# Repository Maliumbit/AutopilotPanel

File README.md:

# AutopilotPanel
Autopilot Controller

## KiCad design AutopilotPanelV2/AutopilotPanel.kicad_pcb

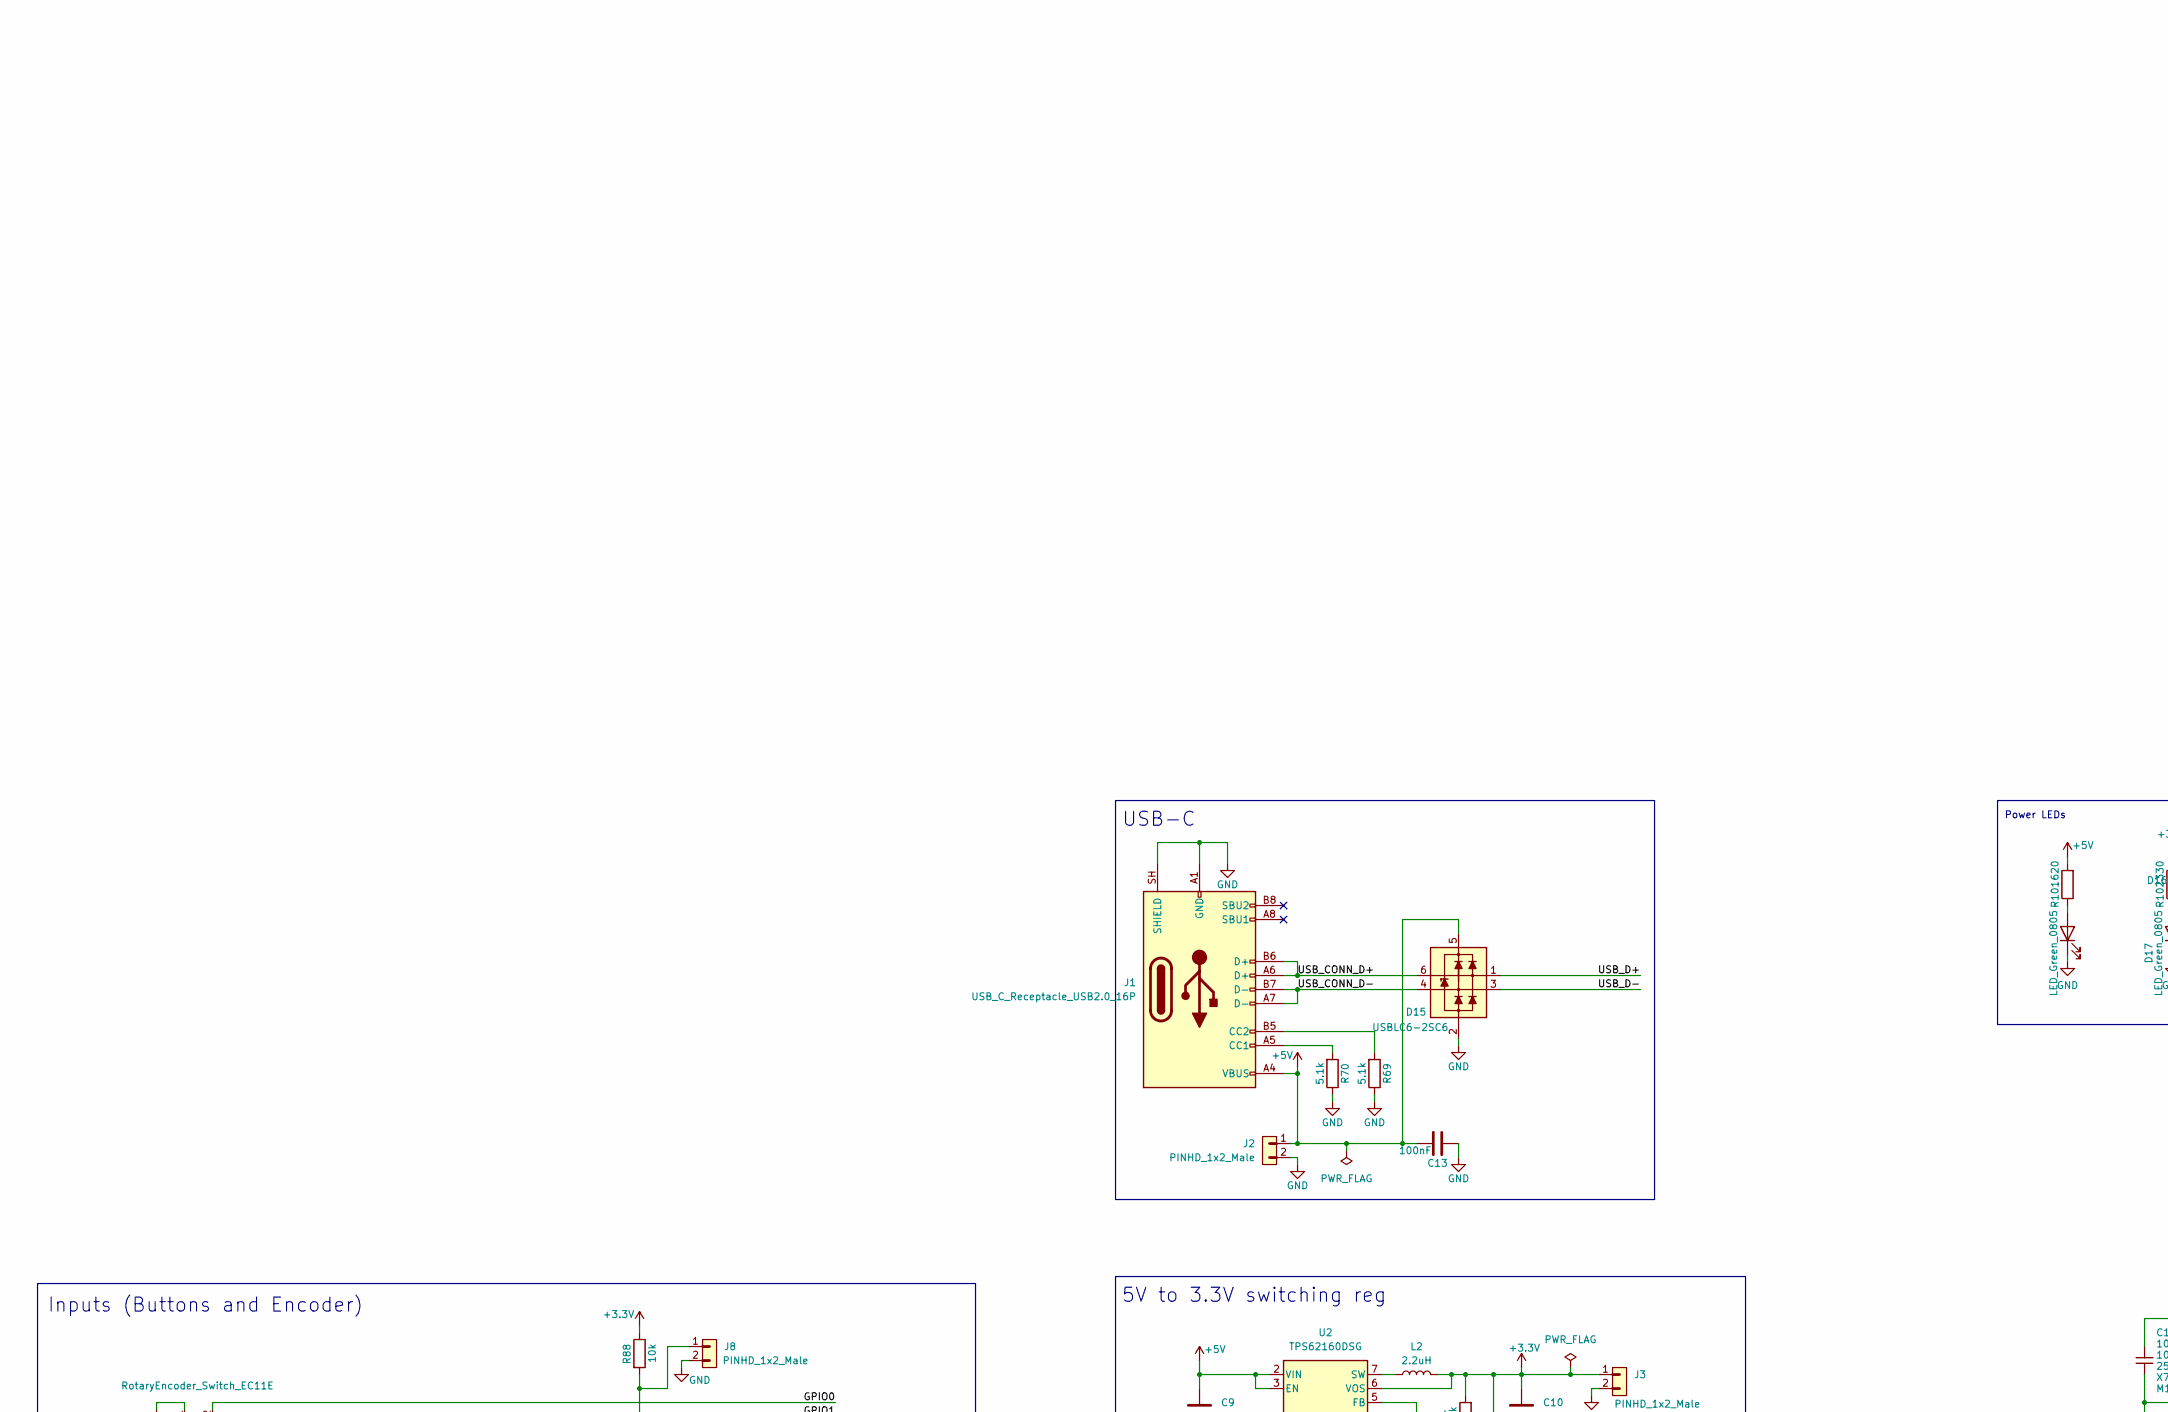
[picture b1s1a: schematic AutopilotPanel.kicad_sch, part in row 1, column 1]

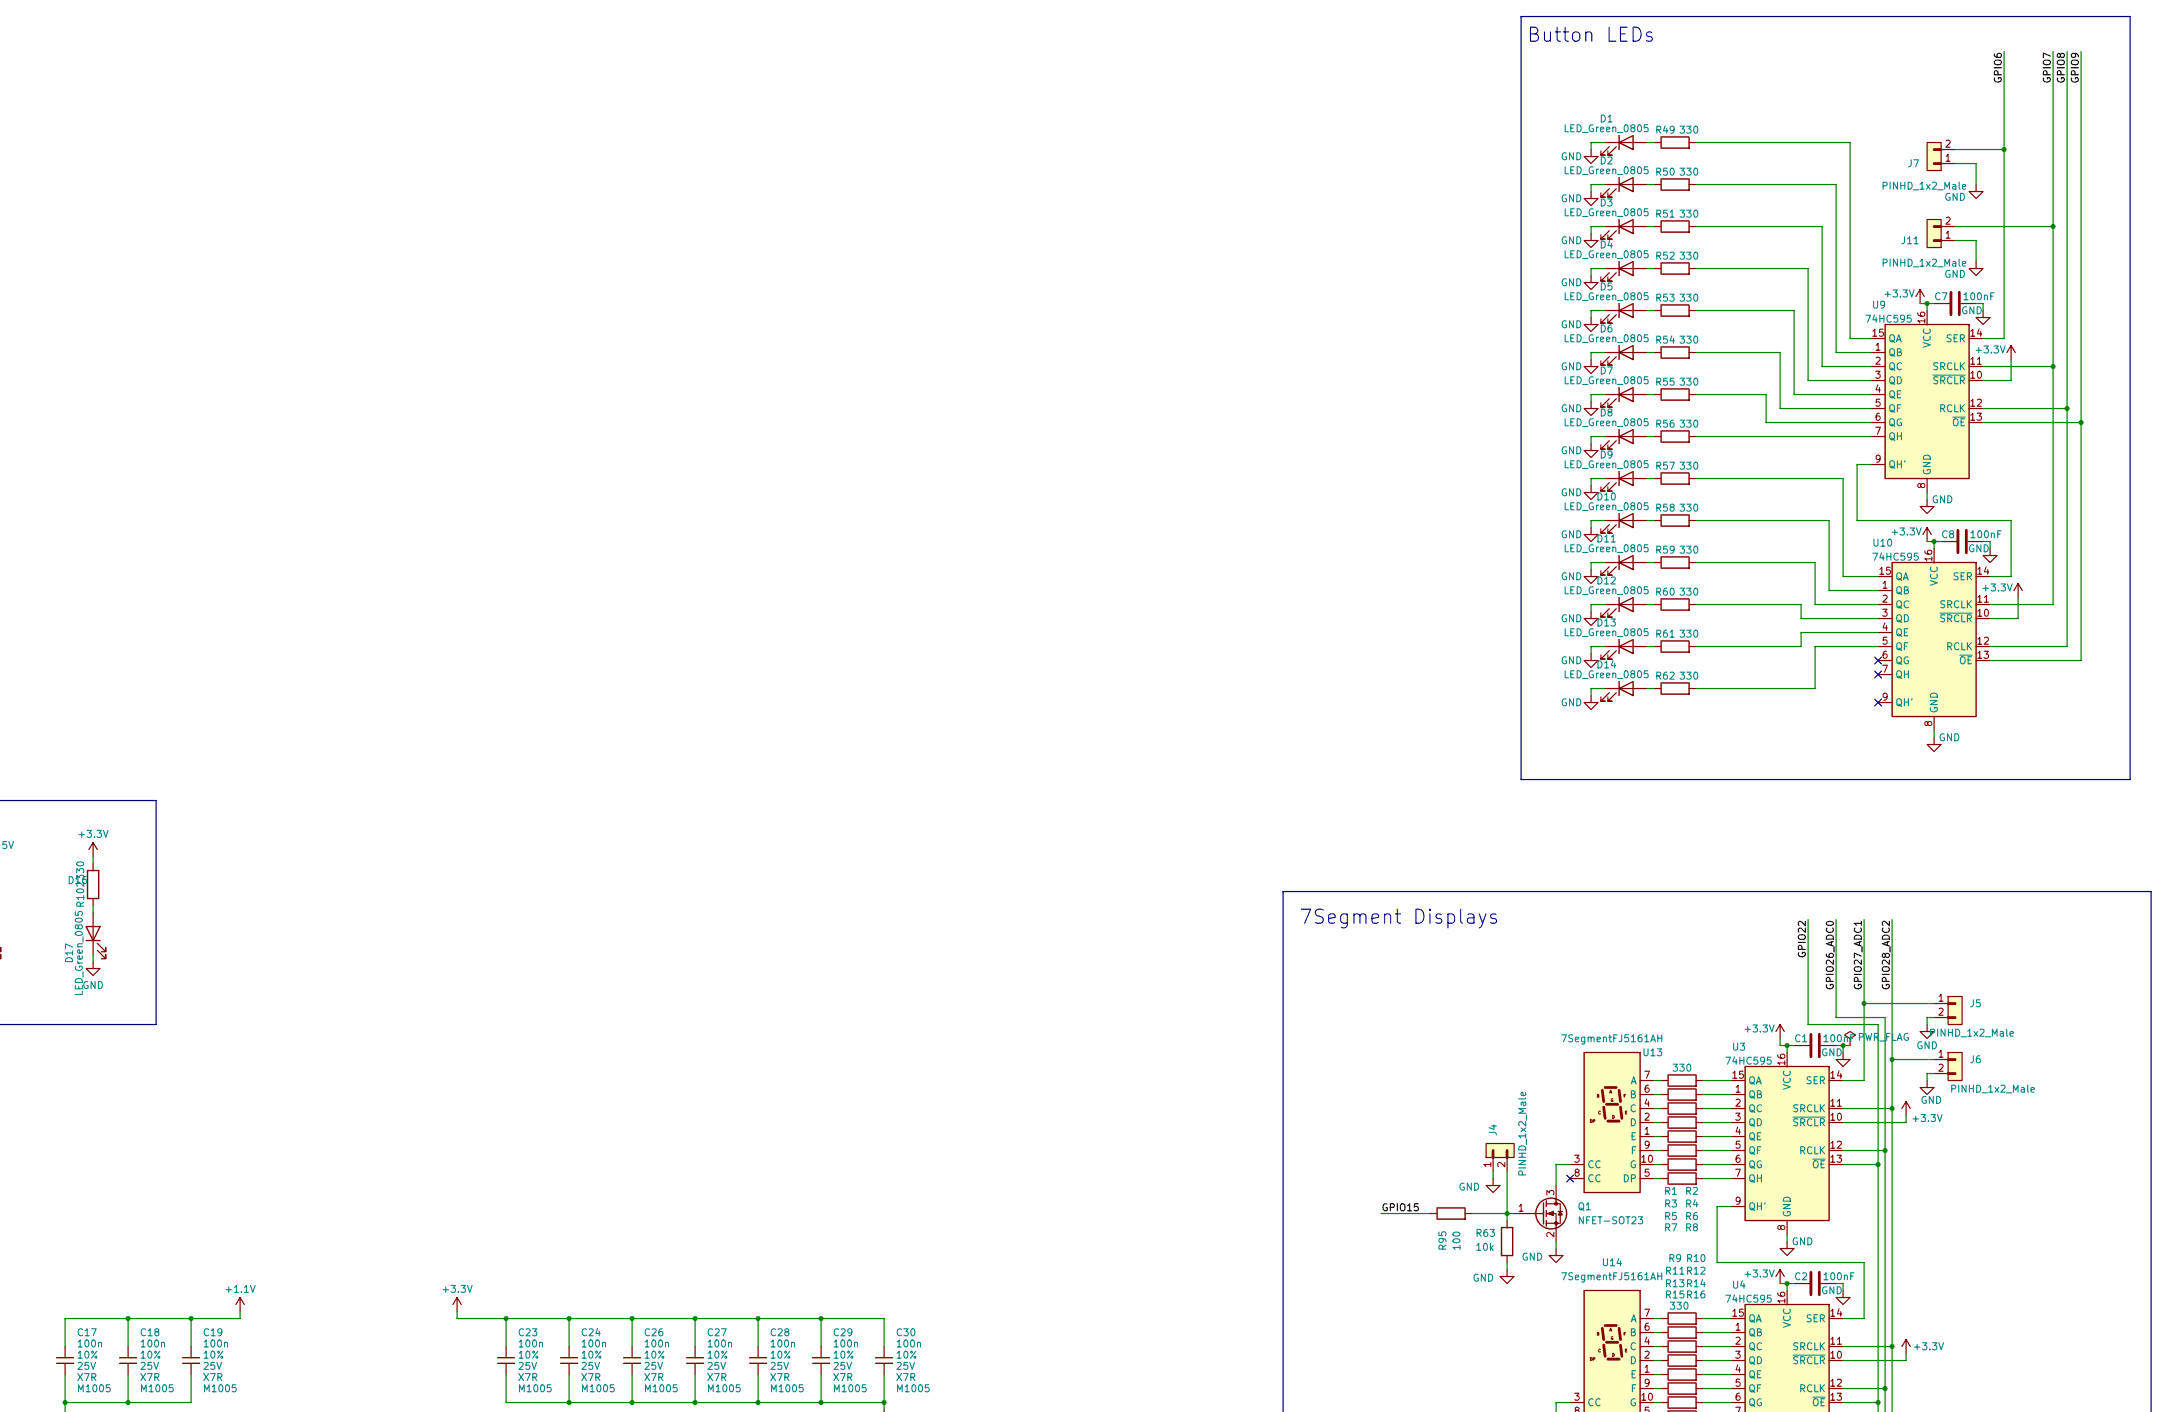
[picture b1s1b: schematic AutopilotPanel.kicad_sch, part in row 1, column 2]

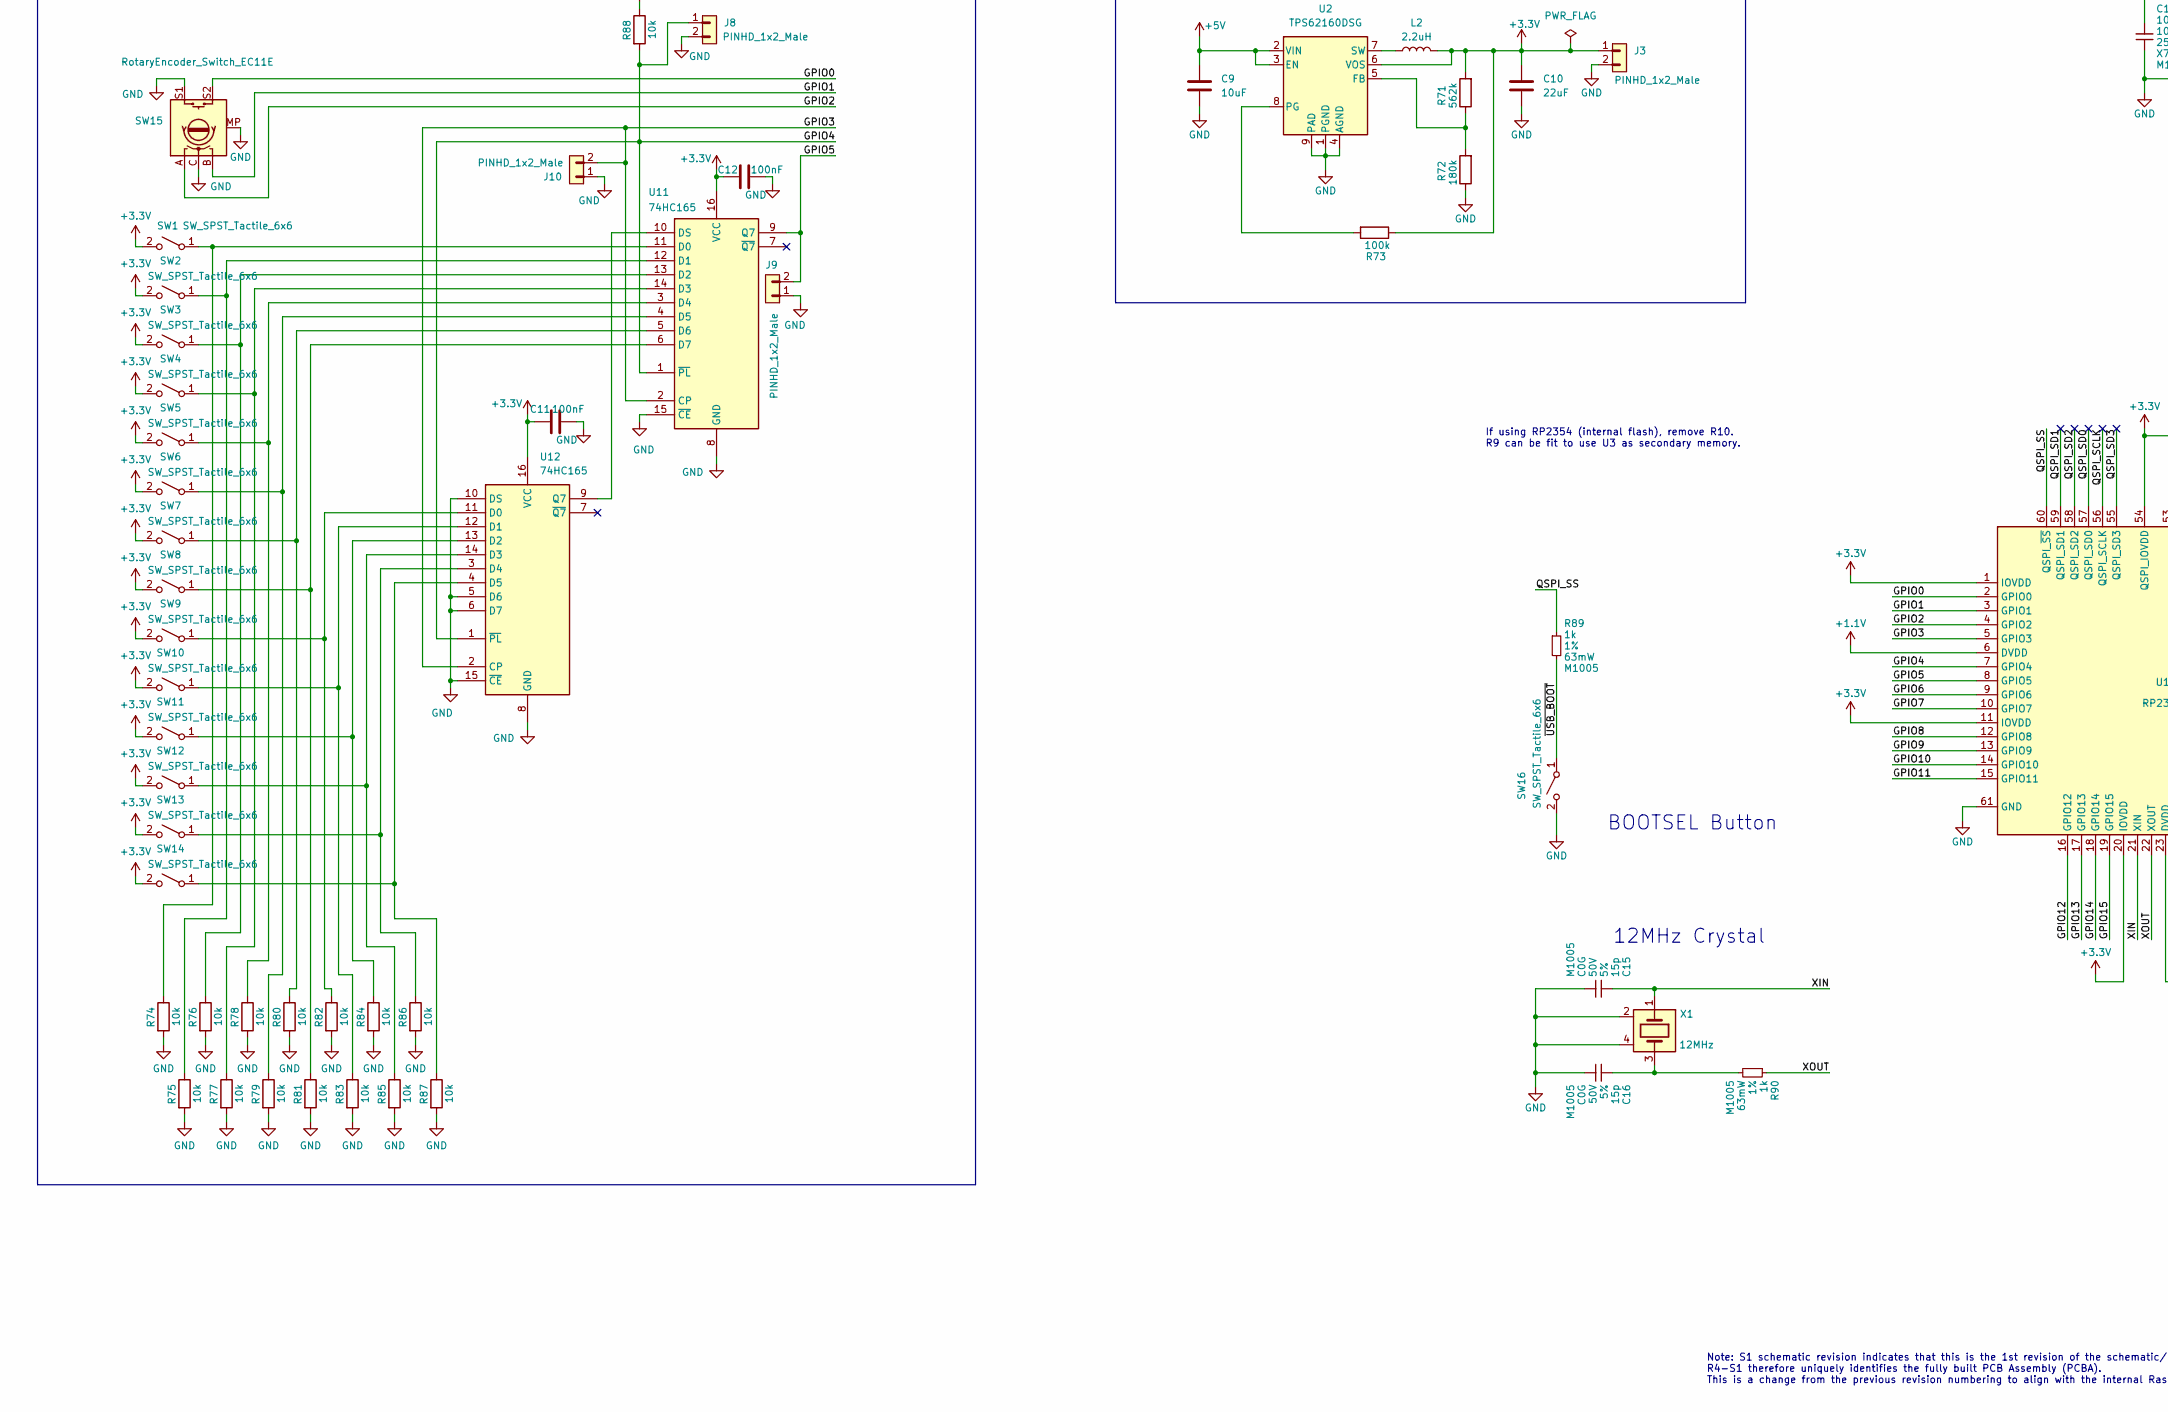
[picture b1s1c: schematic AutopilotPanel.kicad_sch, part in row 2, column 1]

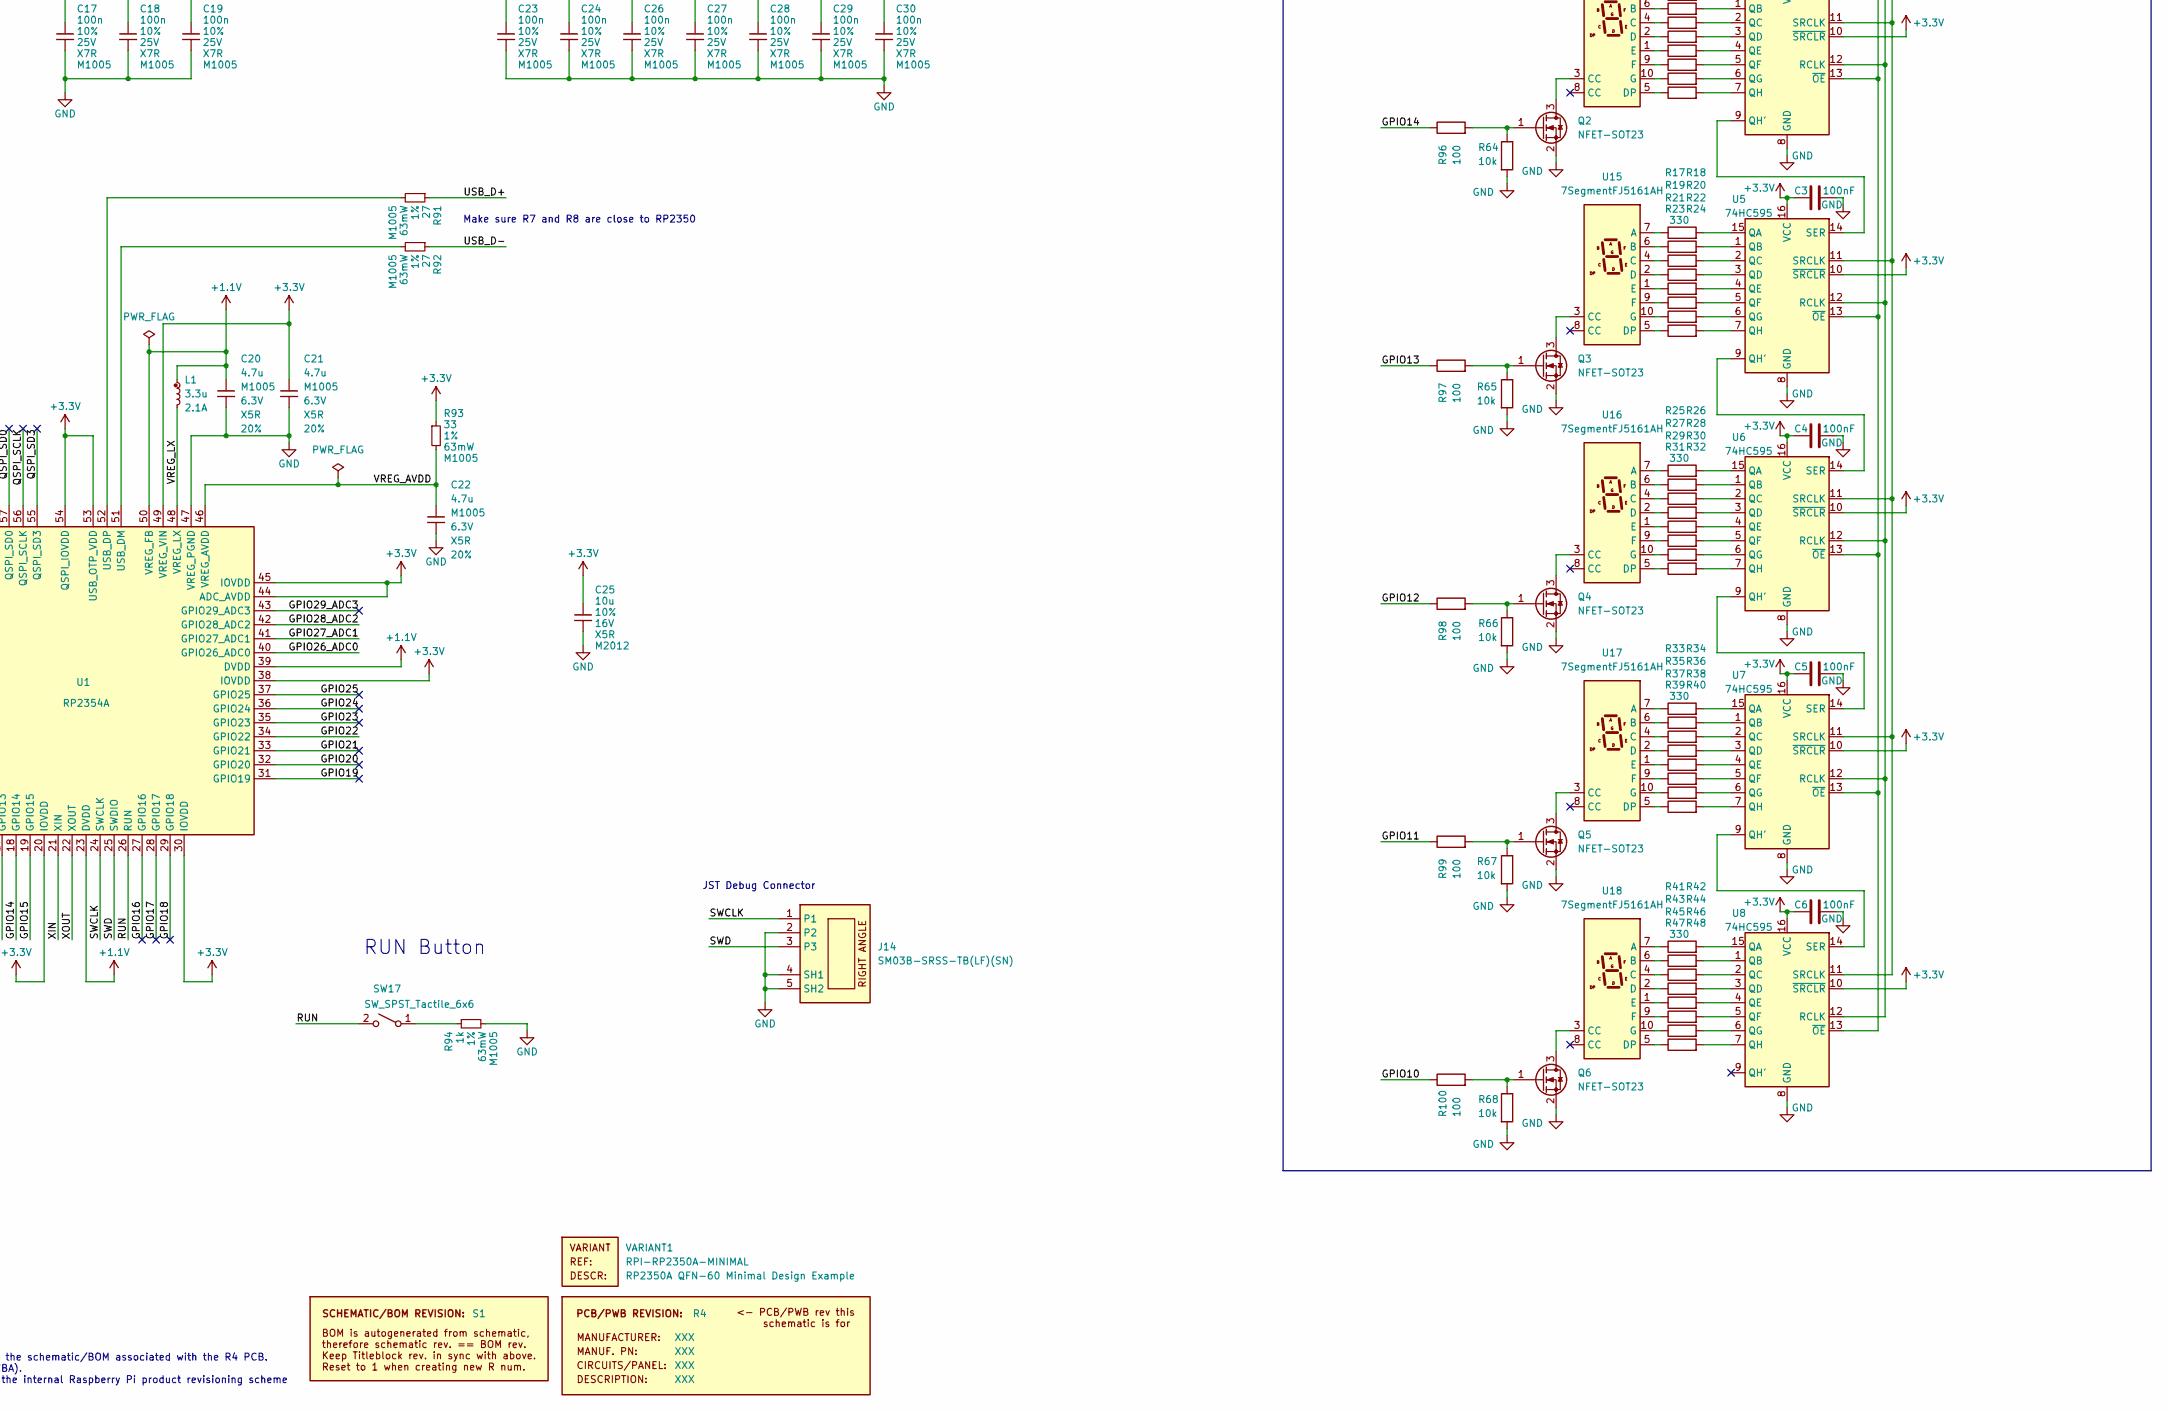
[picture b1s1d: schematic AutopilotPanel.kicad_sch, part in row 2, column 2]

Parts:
C1, C2, C3, C4, C5, C6, C7, C8, C11, C12, C13: 100nF; C_0603_1608Metric
C9: 10uF; C_0805_2012Metric
C10: 22uF; C_0805_2012Metric
C15, C16: 15p; C_0402_1005Metric; voltage 50V; tolerance 5%; part_uid RP-01C89W-LLY9XV
C17, C18, C19, C23, C24, C26, C27, C28, C29, C30: 100n; C_0402_1005Metric; voltage 25V; tolerance 10%; part_uid RP-01BJ9Y-KRGF41
C20, C21, C22: 4.7u; C_0402_1005Metric; voltage 6.3V; tolerance 20%; part_uid RP-019A1P-0C2GHY
C25: 10u; C_0805_2012Metric; voltage 16V; tolerance 10%; part_uid RP-01GYSK-AVBE41
D1, D2, D3, D4, D5, D6, D7, D8, D9, D10, D11, D12, D13, D14, D16, D17: LED_Green_0805; LED_0805_2012Metric_Pad1.15x1.40mm_HandSolder
D15: USBLC6-2SC6; SOT-23-6
J1: USB_C_Receptacle_USB2.0_16P; USB_C_Receptacle_G-Switch_GT-USB-7010ASV
J2, J3, J4, J5, J6, J7, J8, J9, J10, J11: PINHD_1x2_Male; PinHeader_1x02_P2.54mm_Vertical
J14: SM03B-SRSS-TB(LF)(SN); jst_sm03b-srss-tb-lf--sn-; part_uid RP-01EKJ1-8V9SV1
L1: 3.3u; abracon_aota-b201610s3r3-101-t; tolerance 20%; part_uid RP-01GY5D-2VC7WP
L2: 2.2uH; L_Changjiang_FNR3015S
PCB1: R4; manufacturer_pn XXX
Q1, Q2, Q3, Q4, Q5, Q6: NFET-SOT23; SOT-23
R1, R2, R3, R4, R5, R6, R7, R8, R9, R10, R11, R12, R13, R14, R15, R16, R17, R18, R19, R20, R21, R22, R23, R24, R25, R26, R27, R28, R29, R30, R31, R32, R33, R34, R35, R36, R37, R38, R39, R40, R41, R42, R43, R44, R45, R46, R47, R48, R49, R50, R51, R52, R53, R54, R55, R56, R57, R58, R59, R60, R61, R62, R102: 330; R_0603_1608Metric
R63, R64, R65, R66, R67, R68, R74, R75, R76, R77, R78, R79, R80, R81, R82, R83, R84, R85, R86, R87, R88: 10k; R_0603_1608Metric
R69, R70: 5.1k; R_0603_1608Metric
R71: 562k; R_0603_1608Metric
R72: 180k; R_0603_1608Metric
R73: 100k; R_0603_1608Metric
R89, R90, R94: 1k; R_0402_1005Metric; tolerance 1%; voltage 50V; part_uid RP-019A1P-4Z6ZWY
R91, R92: 27; R_0402_1005Metric; tolerance 1%; voltage 50V; part_uid RP-01C89V-LTEYC4
R93: 33; R_0402_1005Metric; tolerance 1%; voltage 50V; part_uid RP-019A1P-58PW9L
R95, R96, R97, R98, R99, R100: 100; R_0603_1608Metric
R101: 620; R_0603_1608Metric
SBREV1: S1
SW1, SW2, SW3, SW4, SW5, SW6, SW7, SW8, SW9, SW10, SW11, SW12, SW13, SW14, SW16, SW17: SW_SPST_Tactile_6x6; SW_Push_1P1T_NO_E-Switch_TL3301NxxxxxG
SW15: RotaryEncoder_Switch_EC11E; RotaryEncoder_Alps_EC11E-Switch_Vertical_H20mm
U1: RP2354A; rpi_rp2350a_vias; part_uid RP-01HA9H-9K5E8T
U2: TPS62160DSG; Texas_DSG0008A_WSON-8-1EP_2x2mm_P0.5mm_EP0.9x1.6mm_ThermalV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
U3, U4, U5, U6, U7, U8, U9, U10: 74HC595; TSSOP-16_4.4x5mm_P0.65mm
U11, U12: 74HC165; TSSOP-16_4.4x5mm_P0.65mm
U13, U14, U15, U16, U17, U18: 7SegmentFJ5161AH; D1X8K
VARIANT1: RPI-RP2350A-MINIMAL
X1: 12MHz; generic_xtalcc320x250x80-4; tolerance 30ppm; part_uid RP-01G8X7-GS352B

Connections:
+1.1V: C17.1, C18.1, C19.1, C20.1, L1.1, U1.6 (DVDD), U1.23 (DVDD), U1.39 (DVDD), U1.50 (VREG_FB)
+3.3V: C1.1, C2.1, C3.1, C4.1, C5.1, C6.1, C7.1, C8.1, C10.1, C11.1, C12.1, C21.1, C23.1, C24.1, C25.1, C26.1, C27.1, C28.1, C29.1, C30.1, J3.1, L2.2, R71.2, R73.1, R88.1, R93.1, R102.2, SW1.2 (B), SW2.2 (B), SW3.2 (B), SW4.2 (B), SW5.2 (B), SW6.2 (B), SW7.2 (B), SW8.2 (B), SW9.2 (B), SW10.2 (B), SW11.2 (B), SW12.2 (B), SW13.2 (B), SW14.2 (B), U1.1 (IOVDD), U1.11 (IOVDD), U1.20 (IOVDD), U1.30 (IOVDD), U1.38 (IOVDD), U1.44 (ADC_AVDD), U1.45 (IOVDD), U1.49 (VREG_VIN), U1.53 (USB_OTP_VDD), U1.54 (QSPI_IOVDD), U2.6 (VOS), U3.10 (~SRCLR), U3.16 (VCC), U4.10 (~SRCLR), U4.16 (VCC), U5.10 (~SRCLR), U5.16 (VCC), U6.10 (~SRCLR), U6.16 (VCC), U7.10 (~SRCLR), U7.16 (VCC), U8.10 (~SRCLR), U8.16 (VCC), U9.10 (~SRCLR), U9.16 (VCC), U10.10 (~SRCLR), U10.16 (VCC), U11.16 (VCC), U12.16 (VCC)
+5V: C9.1, C13.2, D15.5 (VP), J1.A4 (VBUS), J1.A9 (VBUS), J1.B4 (VBUS), J1.B9 (VBUS), J2.1, R101.2, U2.2 (VIN), U2.3 (EN)
/GPIO0: SW15.S2, U1.2 (GPIO0)
/GPIO1: SW15.B, U1.3 (GPIO1)
/GPIO2: SW15.A, U1.4 (GPIO2)
/GPIO3: J10.2, U1.5 (GPIO3), U11.2 (CP), U12.2 (CP)
/GPIO4: J8.1, R88.2, U1.7 (GPIO4), U11.1 (~PL), U12.1 (~PL)
/GPIO5: J9.2, U1.8 (GPIO5), U11.9 (Q7)
/GPIO6: J7.2, U1.9 (GPIO6), U9.14 (SER)
/GPIO7: J11.2, U1.10 (GPIO7), U9.11 (SRCLK), U10.11 (SRCLK)
/GPIO8: U1.12 (GPIO8), U9.12 (RCLK), U10.12 (RCLK)
/GPIO9: U1.13 (GPIO9), U9.13 (~OE), U10.13 (~OE)
/GPIO10: R100.1, U1.14 (GPIO10)
/GPIO11: R99.1, U1.15 (GPIO11)
/GPIO12: R98.1, U1.16 (GPIO12)
/GPIO13: R97.1, U1.17 (GPIO13)
/GPIO14: R96.1, U1.18 (GPIO14)
/GPIO15: R95.1, U1.19 (GPIO15)
/GPIO16: U1.27 (GPIO16)
/GPIO17: U1.28 (GPIO17)
/GPIO18: U1.29 (GPIO18)
/GPIO19: U1.31 (GPIO19)
/GPIO20: U1.32 (GPIO20)
/GPIO21: U1.33 (GPIO21)
/GPIO22: U1.34 (GPIO22), U3.13 (~OE), U4.13 (~OE), U5.13 (~OE), U6.13 (~OE), U7.13 (~OE), U8.13 (~OE)
/GPIO23: U1.35 (GPIO23)
/GPIO24: U1.36 (GPIO24)
/GPIO25: U1.37 (GPIO25)
/GPIO26_ADC0: U1.40 (GPIO26_ADC0), U3.12 (RCLK), U4.12 (RCLK), U5.12 (RCLK), U6.12 (RCLK), U7.12 (RCLK), U8.12 (RCLK)
/GPIO27_ADC1: J5.1, U1.41 (GPIO27_ADC1), U3.14 (SER)
/GPIO28_ADC2: J6.1, U1.42 (GPIO28_ADC2), U3.11 (SRCLK), U4.11 (SRCLK), U5.11 (SRCLK), U6.11 (SRCLK), U7.11 (SRCLK), U8.11 (SRCLK)
/GPIO29_ADC3: U1.43 (GPIO29_ADC3)
/QSPI_SCLK: U1.56 (QSPI_SCLK)
/QSPI_SD0: U1.57 (QSPI_SD0)
/QSPI_SD1: U1.59 (QSPI_SD1)
/QSPI_SD2: U1.58 (QSPI_SD2)
/QSPI_SD3: U1.55 (QSPI_SD3)
/QSPI_SS: R89.1, U1.60 (QSPI_~SS)
/RUN: SW17.2 (B), U1.26 (RUN)
/SWCLK: J14.1, U1.24 (SWCLK)
/SWD: J14.3, U1.25 (SWDIO)
/USB_CONN_D+: D15.6 (L1), J1.A6 (D+), J1.B6 (D+)
/USB_CONN_D-: D15.4 (L2), J1.A7 (D-), J1.B7 (D-)
/USB_D+: D15.1 (L1), R91.1
/USB_D-: D15.3 (L2), R92.1
/VREG_AVDD: C22.1, R93.2, U1.46 (VREG_AVDD)
/VREG_LX: L1.2, U1.48 (VREG_LX)
/XIN: C15.1, U1.21 (XIN), X1.1
/XOUT: R90.1, U1.22 (XOUT)
/~USB_BOOT: R89.2, SW16.1 (A)
GND: C1.2, C2.2, C3.2, C4.2, C5.2, C6.2, C7.2, C8.2, C9.2, C10.2, C11.2, C12.2, C13.1, C15.2, C16.2, C17.2, C18.2, C19.2, C20.2, C21.2, C22.2, C23.2, C24.2, C25.2, C26.2, C27.2, C28.2, C29.2, C30.2, D1.1 (K), D2.1 (K), D3.1 (K), D4.1 (K), D5.1 (K), D6.1 (K), D7.1 (K), D8.1 (K), D9.1 (K), D10.1 (K), D11.1 (K), D12.1 (K), D13.1 (K), D14.1 (K), D15.2 (VN), D16.1 (K), D17.1 (K), J1.A1 (GND), J1.A12 (GND), J1.B1 (GND), J1.B12 (GND), J1.SH (SHIELD), J2.2, J3.2, J4.1, J5.2, J6.2, J7.1, J8.2, J9.1, J10.1, J11.1, J14.2, J14.4 (SH1), J14.5 (SH2), Q1.2 (S), Q2.2 (S), Q3.2 (S), Q4.2 (S), Q5.2 (S), Q6.2 (S), R63.2, R64.2, R65.2, R66.2, R67.2, R68.2, R69.1, R70.1, R72.1, R74.2, R75.2, R76.2, R77.2, R78.2, R79.2, R80.2, R81.2, R82.2, R83.2, R84.2, R85.2, R86.2, R87.2, R94.2, SW15.C, SW15.MP, SW15.S1, SW16.2 (B), U1.47 (VREG_PGND), U1.61 (GND), U2.1 (PGND), U2.4 (AGND), U2.9 (PAD), U3.8 (GND), U4.8 (GND), U5.8 (GND), U6.8 (GND), U7.8 (GND), U8.8 (GND), U9.8 (GND), U10.8 (GND), U11.8 (GND), U11.15 (~CE), U12.5 (D6), U12.6 (D7), U12.8 (GND), U12.10 (DS), U12.15 (~CE), X1.2, X1.4
unnamed: C16.1, R90.2, X1.3
unnamed: D1.2 (A), R49.1
unnamed: D2.2 (A), R50.1
unnamed: D3.2 (A), R51.1
unnamed: D4.2 (A), R52.1
unnamed: D5.2 (A), R53.1
unnamed: D6.2 (A), R54.1
unnamed: D7.2 (A), R55.1
unnamed: D8.2 (A), R56.1
unnamed: D9.2 (A), R57.1
unnamed: D10.2 (A), R58.1
unnamed: D11.2 (A), R59.1
unnamed: D12.2 (A), R60.1
unnamed: D13.2 (A), R61.1
unnamed: D14.2 (A), R62.1
unnamed: D16.2 (A), R101.1
unnamed: D17.2 (A), R102.1
unnamed: J1.A5 (CC1), R70.2
unnamed: J1.B5 (CC2), R69.2
unnamed: Q1.3 (D), U13.3 (CC)
unnamed: J4.2, Q1.1 (G), R63.1, R95.2
unnamed: Q2.3 (D), U14.3 (CC)
unnamed: Q2.1 (G), R64.1, R96.2
unnamed: Q3.3 (D), U15.3 (CC)
unnamed: Q3.1 (G), R65.1, R97.2
unnamed: Q4.3 (D), U16.3 (CC)
unnamed: Q4.1 (G), R66.1, R98.2
unnamed: Q5.3 (D), U17.3 (CC)
unnamed: Q5.1 (G), R67.1, R99.2
unnamed: Q6.3 (D), U18.3 (CC)
unnamed: Q6.1 (G), R68.1, R100.2
unnamed: R74.1, SW1.1 (A), U11.11 (D0)
unnamed: R75.1, SW2.1 (A), U11.12 (D1)
unnamed: R76.1, SW3.1 (A), U11.13 (D2)
unnamed: R77.1, SW4.1 (A), U11.14 (D3)
unnamed: R78.1, SW5.1 (A), U11.3 (D4)
unnamed: R79.1, SW6.1 (A), U11.4 (D5)
unnamed: R80.1, SW7.1 (A), U11.5 (D6)
unnamed: R81.1, SW8.1 (A), U11.6 (D7)
unnamed: R82.1, SW9.1 (A), U12.11 (D0)
unnamed: R83.1, SW10.1 (A), U12.12 (D1)
unnamed: R84.1, SW11.1 (A), U12.13 (D2)
unnamed: R85.1, SW12.1 (A), U12.14 (D3)
unnamed: R86.1, SW13.1 (A), U12.3 (D4)
unnamed: R87.1, SW14.1 (A), U12.4 (D5)
unnamed: R94.1, SW17.1 (A)
unnamed: R92.2, U1.51 (USB_DM)
unnamed: R91.2, U1.52 (USB_DP)
unnamed: R71.1, R72.2, U2.5 (FB)
unnamed: R73.2, U2.8 (PG)
unnamed: L2.1, U2.7 (SW)
unnamed: R1.2, U3.15 (QA)
unnamed: R2.2, U3.1 (QB)
unnamed: R3.2, U3.2 (QC)
unnamed: R4.2, U3.3 (QD)
unnamed: R5.2, U3.4 (QE)
unnamed: R6.2, U3.5 (QF)
unnamed: R7.2, U3.6 (QG)
unnamed: U3.9 (QH'), U4.14 (SER)
unnamed: R8.2, U3.7 (QH)
unnamed: R9.2, U4.15 (QA)
unnamed: R10.2, U4.1 (QB)
unnamed: R11.2, U4.2 (QC)
unnamed: R12.2, U4.3 (QD)
unnamed: R13.2, U4.4 (QE)
unnamed: R14.2, U4.5 (QF)
unnamed: R15.2, U4.6 (QG)
unnamed: U4.9 (QH'), U5.14 (SER)
unnamed: R16.2, U4.7 (QH)
unnamed: R17.2, U5.15 (QA)
unnamed: R18.2, U5.1 (QB)
unnamed: R19.2, U5.2 (QC)
unnamed: R20.2, U5.3 (QD)
unnamed: R21.2, U5.4 (QE)
unnamed: R22.2, U5.5 (QF)
unnamed: R23.2, U5.6 (QG)
unnamed: U5.9 (QH'), U6.14 (SER)
unnamed: R24.2, U5.7 (QH)
unnamed: R25.2, U6.15 (QA)
unnamed: R26.2, U6.1 (QB)
unnamed: R27.2, U6.2 (QC)
unnamed: R28.2, U6.3 (QD)
unnamed: R29.2, U6.4 (QE)
unnamed: R30.2, U6.5 (QF)
unnamed: R31.2, U6.6 (QG)
unnamed: U6.9 (QH'), U7.14 (SER)
unnamed: R32.2, U6.7 (QH)
unnamed: R33.2, U7.15 (QA)
unnamed: R34.2, U7.1 (QB)
unnamed: R35.2, U7.2 (QC)
unnamed: R36.2, U7.3 (QD)
unnamed: R37.2, U7.4 (QE)
unnamed: R38.2, U7.5 (QF)
unnamed: R39.2, U7.6 (QG)
unnamed: U7.9 (QH'), U8.14 (SER)
unnamed: R40.2, U7.7 (QH)
unnamed: R41.2, U8.15 (QA)
unnamed: R42.2, U8.1 (QB)
unnamed: R43.2, U8.2 (QC)
unnamed: R44.2, U8.3 (QD)
unnamed: R45.2, U8.4 (QE)
unnamed: R46.2, U8.5 (QF)
unnamed: R47.2, U8.6 (QG)
unnamed: R48.2, U8.7 (QH)
unnamed: R49.2, U9.15 (QA)
unnamed: R50.2, U9.1 (QB)
unnamed: R51.2, U9.2 (QC)
unnamed: R52.2, U9.3 (QD)
unnamed: R53.2, U9.4 (QE)
unnamed: R54.2, U9.5 (QF)
unnamed: R55.2, U9.6 (QG)
unnamed: R56.2, U9.7 (QH)
unnamed: R57.2, U10.15 (QA)
unnamed: R58.2, U10.1 (QB)
unnamed: R59.2, U10.2 (QC)
unnamed: R60.2, U10.3 (QD)
unnamed: R61.2, U10.4 (QE)
unnamed: R62.2, U10.5 (QF)
unnamed: U9.9 (QH'), U10.14 (SER)
unnamed: U11.10 (DS), U12.9 (Q7)
unnamed: R1.1, U13.7 (A)
unnamed: R2.1, U13.6 (B)
unnamed: R3.1, U13.4 (C)
unnamed: R4.1, U13.2 (D)
unnamed: R8.1, U13.5 (DP)
unnamed: R5.1, U13.1 (E)
unnamed: R6.1, U13.9 (F)
unnamed: R7.1, U13.10 (G)
unnamed: R9.1, U14.7 (A)
unnamed: R10.1, U14.6 (B)
unnamed: R11.1, U14.4 (C)
unnamed: R12.1, U14.2 (D)
unnamed: R16.1, U14.5 (DP)
unnamed: R13.1, U14.1 (E)
unnamed: R14.1, U14.9 (F)
unnamed: R15.1, U14.10 (G)
unnamed: R17.1, U15.7 (A)
unnamed: R18.1, U15.6 (B)
unnamed: R19.1, U15.4 (C)
unnamed: R20.1, U15.2 (D)
unnamed: R24.1, U15.5 (DP)
unnamed: R21.1, U15.1 (E)
unnamed: R22.1, U15.9 (F)
unnamed: R23.1, U15.10 (G)
unnamed: R25.1, U16.7 (A)
unnamed: R26.1, U16.6 (B)
unnamed: R27.1, U16.4 (C)
unnamed: R28.1, U16.2 (D)
unnamed: R32.1, U16.5 (DP)
unnamed: R29.1, U16.1 (E)
unnamed: R30.1, U16.9 (F)
unnamed: R31.1, U16.10 (G)
unnamed: R33.1, U17.7 (A)
unnamed: R34.1, U17.6 (B)
unnamed: R35.1, U17.4 (C)
unnamed: R36.1, U17.2 (D)
unnamed: R40.1, U17.5 (DP)
unnamed: R37.1, U17.1 (E)
unnamed: R38.1, U17.9 (F)
unnamed: R39.1, U17.10 (G)
unnamed: R41.1, U18.7 (A)
unnamed: R42.1, U18.6 (B)
unnamed: R43.1, U18.4 (C)
unnamed: R44.1, U18.2 (D)
unnamed: R48.1, U18.5 (DP)
unnamed: R45.1, U18.1 (E)
unnamed: R46.1, U18.9 (F)
unnamed: R47.1, U18.10 (G)

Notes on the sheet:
JST Debug Connector
7Segment Displays
RUN Button
Button LEDs
USB-C
BOOTSEL Button
If using RP2354 (internal flash), remove R10. R9 can be fit to use U3 as secondary memory.
Note: S1 schematic revision indicates that this is the 1st revision of the schematic/BOM associated with the R4 PCB. R4-S1 therefore uniquely identifies the fully built PCB Assembly (PCBA). This is a change from the previous revision numbering to align with the internal Raspberry Pi product revisio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
Inputs (Buttons and Encoder)
Make sure R7 and R8 are close to RP2350
5V to 3.3V switching reg
Power LEDs
12MHz Crystal

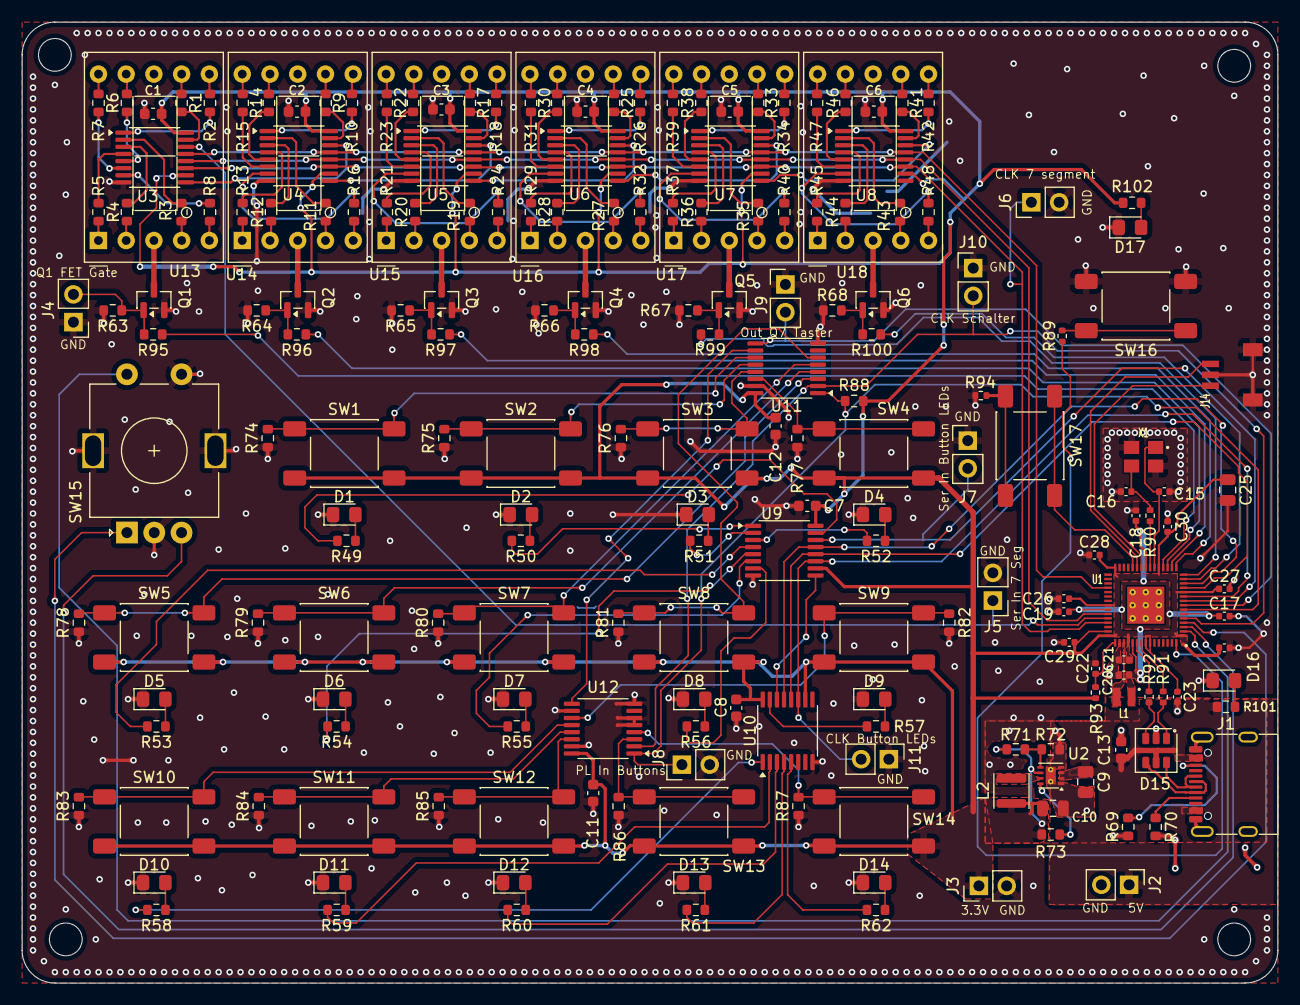
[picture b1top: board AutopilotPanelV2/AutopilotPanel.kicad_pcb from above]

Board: 2 copper layers, 115.0 x 88.0 mm, 204 parts (0 on the bottom side), 205 nets.
